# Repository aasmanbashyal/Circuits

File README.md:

# Circuits
This repo consists the all the circuits i have build

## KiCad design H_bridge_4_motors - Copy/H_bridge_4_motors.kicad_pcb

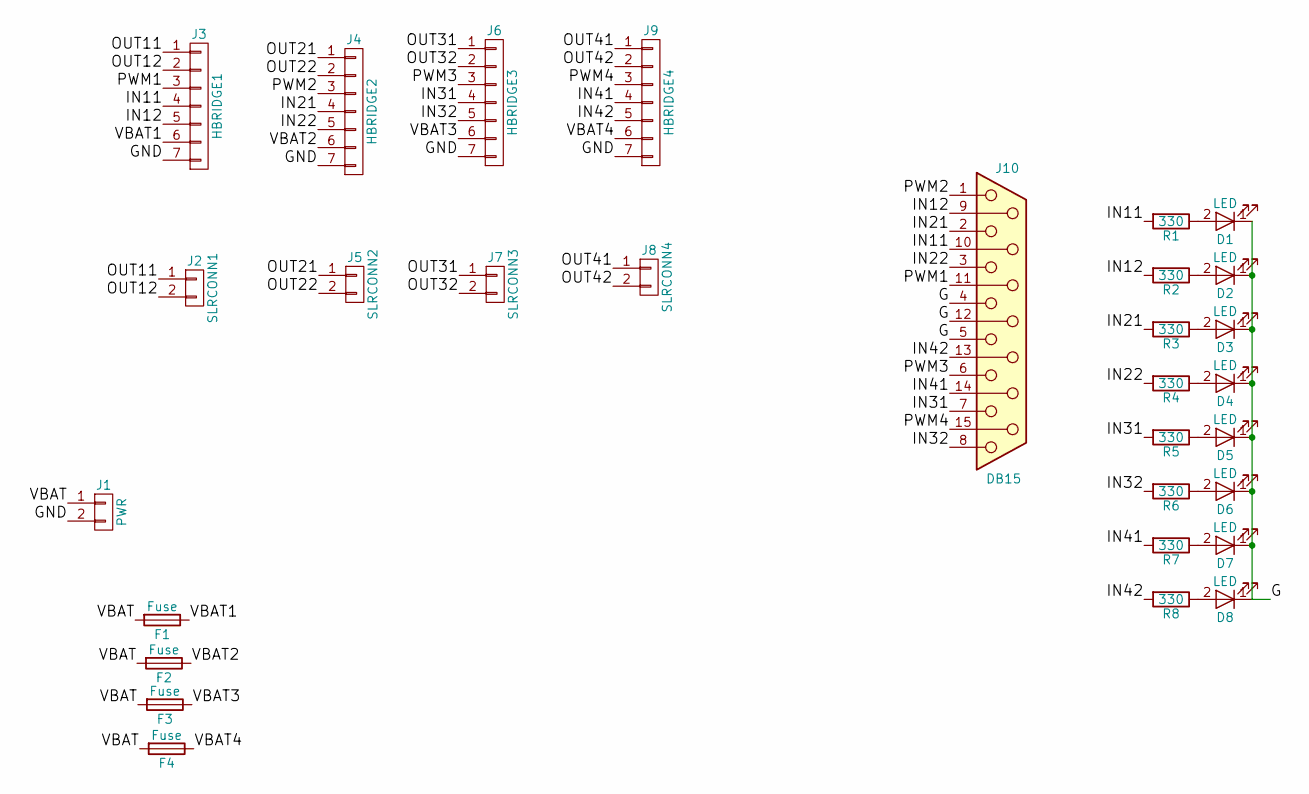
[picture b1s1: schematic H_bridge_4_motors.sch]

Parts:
D1, D2, D3, D4, D5, D6, D7, D8: LED; LED_D3.0mm
F1, F2, F3, F4: Fuse; Fuse_Holder
J1: PWR; Solar_Connector
J2: SLRCONN1; Solar_Connector
J3: HBRIDGE1; Bridge
J4: HBRIDGE2; Bridge
J5: SLRCONN2; Solar_Connector
J6: HBRIDGE3; Bridge
J7: SLRCONN3; Solar_Connector
J8: SLRCONN4; Solar_Connector
J9: HBRIDGE4; Bridge
J10: DB15
R1, R2, R3, R4, R5, R6, R7, R8: 330; Resistor_small

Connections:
/G: D1.1 (K), D2.1 (K), D3.1 (K), D4.1 (K), D5.1 (K), D6.1 (K), D7.1 (K), D8.1 (K), J10.4, J10.5, J10.12
/GND: J1.2, J3.7, J4.7, J6.7, J9.7
/IN11: J3.4, J10.10, R1.2
/IN12: J3.5, J10.9, R2.2
/IN21: J4.4, J10.2, R3.2
/IN22: J4.5, J10.3, R4.2
/IN31: J6.4, J10.7, R5.2
/IN32: J6.5, J10.8, R6.2
/IN41: J9.4, J10.14, R7.2
/IN42: J9.5, J10.13, R8.2
/OUT11: J2.1, J3.1
/OUT12: J2.2, J3.2
/OUT21: J4.1, J5.1
/OUT22: J4.2, J5.2
/OUT31: J6.1, J7.1
/OUT32: J6.2, J7.2
/OUT41: J8.1, J9.1
/OUT42: J8.2, J9.2
/PWM1: J3.3, J10.11 (P111)
/PWM2: J4.3, J10.1
/PWM3: J6.3, J10.6
/PWM4: J9.3, J10.15
/VBAT: F1.2, F2.2, F3.2, F4.2, J1.1
/VBAT1: F1.1, J3.6
/VBAT2: F2.1, J4.6
/VBAT3: F3.1, J6.6
/VBAT4: F4.1, J9.6
unnamed: D1.2 (A), R1.1
unnamed: D2.2 (A), R2.1
unnamed: D3.2 (A), R3.1
unnamed: D4.2 (A), R4.1
unnamed: D5.2 (A), R5.1
unnamed: D6.2 (A), R6.1
unnamed: D7.2 (A), R7.1
unnamed: D8.2 (A), R8.1

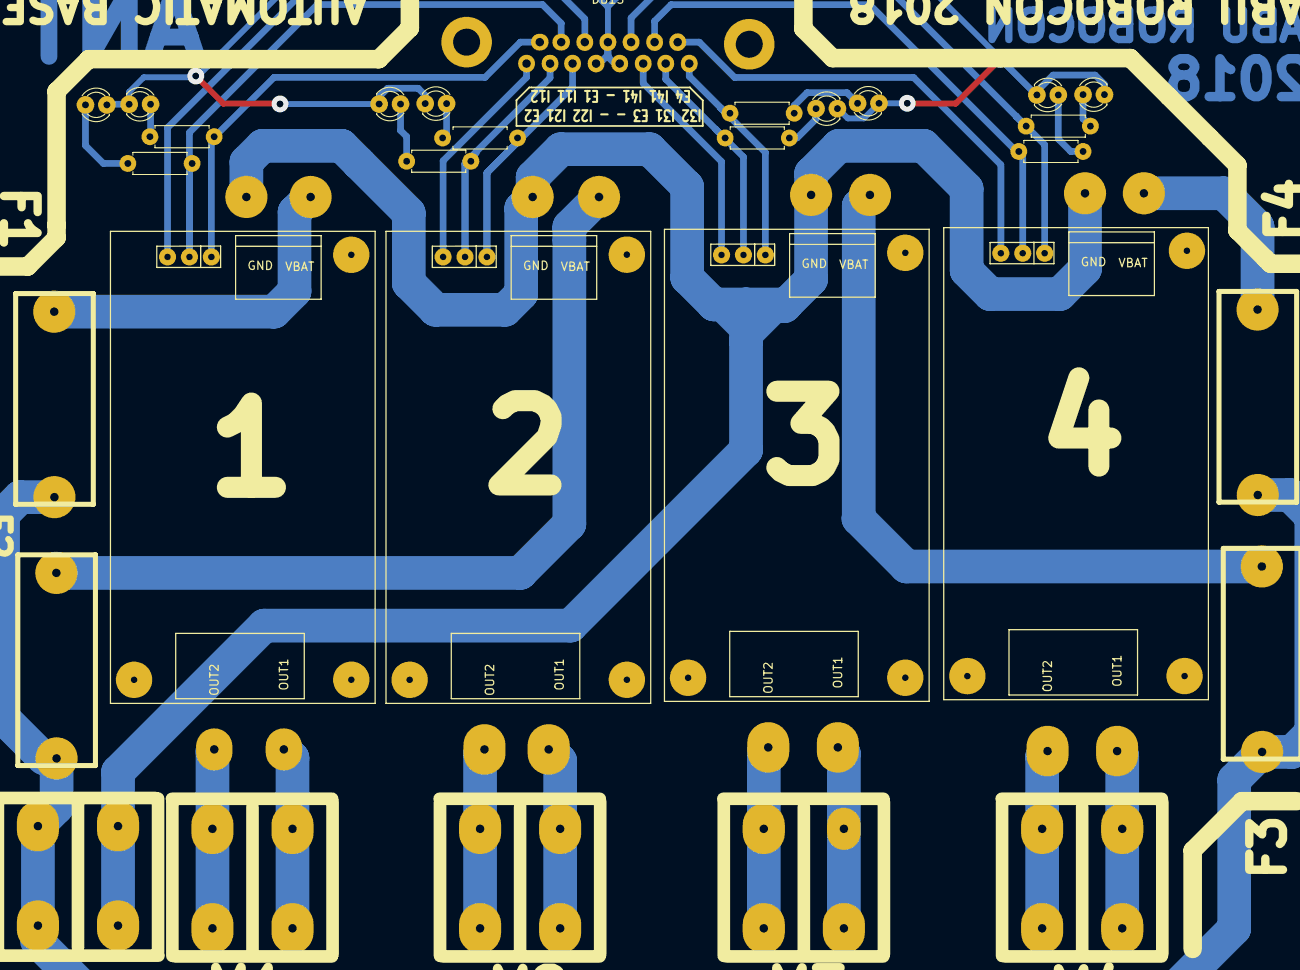
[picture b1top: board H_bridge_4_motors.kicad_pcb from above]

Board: 2 copper layers, 30 parts (0 on the bottom side), 35 nets.

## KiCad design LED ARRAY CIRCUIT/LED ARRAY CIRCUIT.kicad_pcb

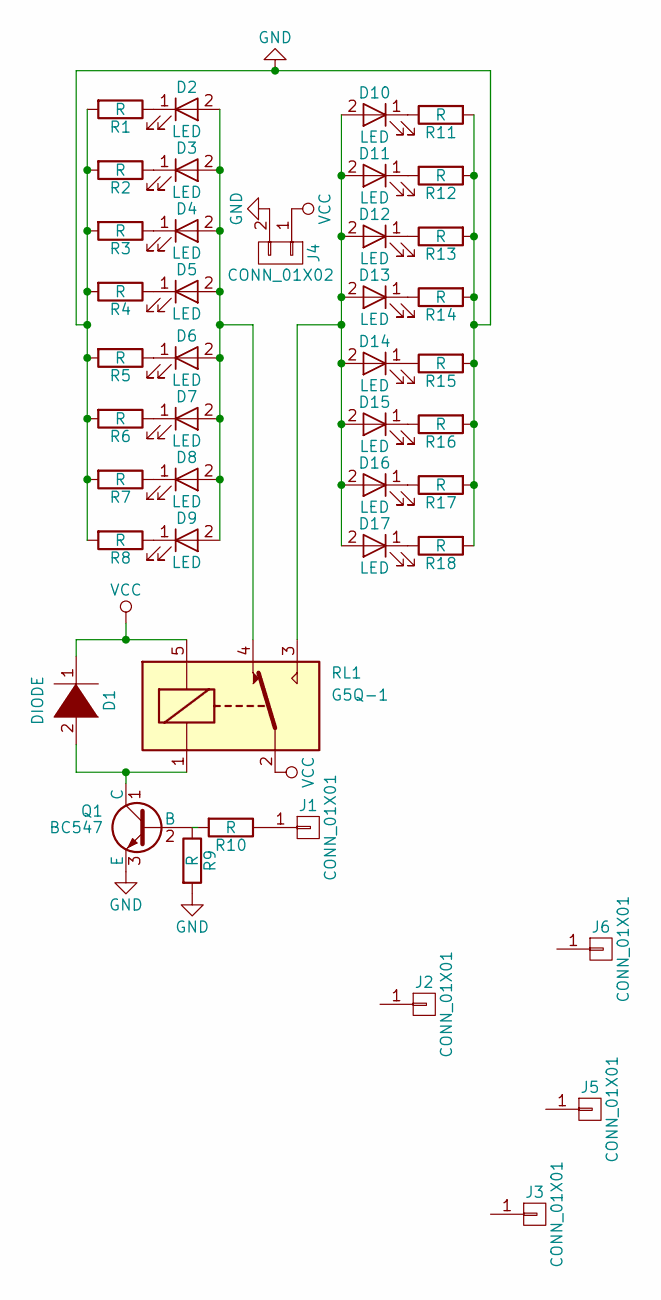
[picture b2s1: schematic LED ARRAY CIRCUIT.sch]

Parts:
D1: DIODE; Diode_Small
D2, D3, D4, D5, D6, D7, D8, D9, D10, D11, D12, D13, D14, D15, D16, D17: LED; LED_D3.0mm
J1: CONN_01X01; Pin_Header_Straight_1x01_Pitch2.00mm
J2, J3, J5, J6: CONN_01X01; 1pin
J4: CONN_01X02; Connector_Bornier_2
Q1: BC547
R1, R2, R3, R4, R5, R6, R7, R8, R9, R10, R11, R12, R13, R14, R15, R16, R17, R18: R; Resistor_small
RL1: G5Q-1; Relay_6V

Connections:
GND: J4.2, Q1.3 (E), R1.2, R2.2, R3.2, R4.2, R5.2, R6.2, R7.2, R8.2, R9.2, R11.2, R12.2, R13.2, R14.2, R15.2, R16.2, R17.2, R18.2
unnamed: D1.2 (A), Q1.1 (C), RL1.1
unnamed: D2.1 (K), R1.1
unnamed: D2.2 (A), D3.2 (A), D4.2 (A), D5.2 (A), D6.2 (A), D7.2 (A), D8.2 (A), D9.2 (A), RL1.4
unnamed: D3.1 (K), R2.1
unnamed: D4.1 (K), R3.1
unnamed: D5.1 (K), R4.1
unnamed: D6.1 (K), R5.1
unnamed: D7.1 (K), R6.1
unnamed: D8.1 (K), R7.1
unnamed: D9.1 (K), R8.1
unnamed: D10.1 (K), R11.1
unnamed: D10.2 (A), D11.2 (A), D12.2 (A), D13.2 (A), D14.2 (A), D15.2 (A), D16.2 (A), D17.2 (A), RL1.3
unnamed: D11.1 (K), R12.1
unnamed: D12.1 (K), R13.1
unnamed: D13.1 (K), R14.1
unnamed: D14.1 (K), R15.1
unnamed: D15.1 (K), R16.1
unnamed: D16.1 (K), R17.1
unnamed: D17.1 (K), R18.1
unnamed: J1.1, R10.1
unnamed: Q1.2 (B), R9.1, R10.2
VCC: D1.1 (K), J4.1, RL1.2, RL1.5

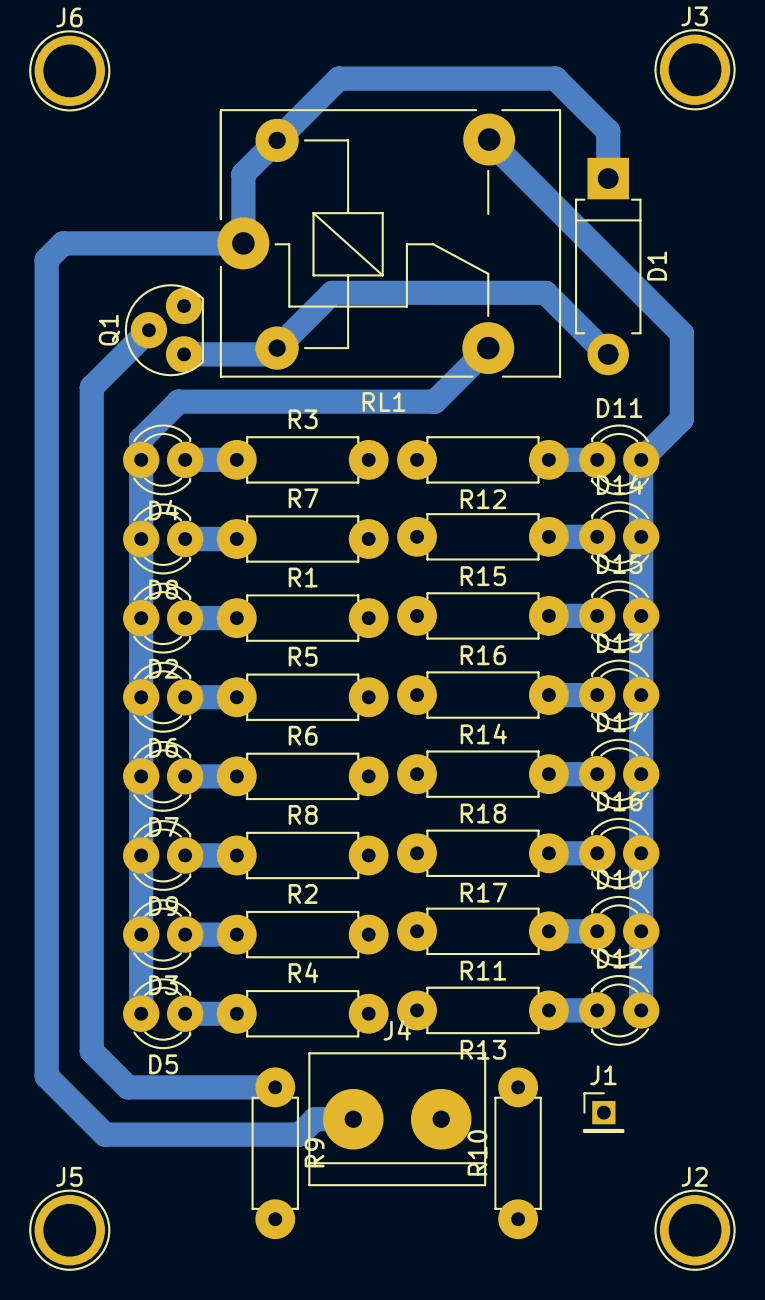
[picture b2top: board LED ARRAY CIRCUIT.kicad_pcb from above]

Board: 2 copper layers, 43 parts (0 on the bottom side), 23 nets.

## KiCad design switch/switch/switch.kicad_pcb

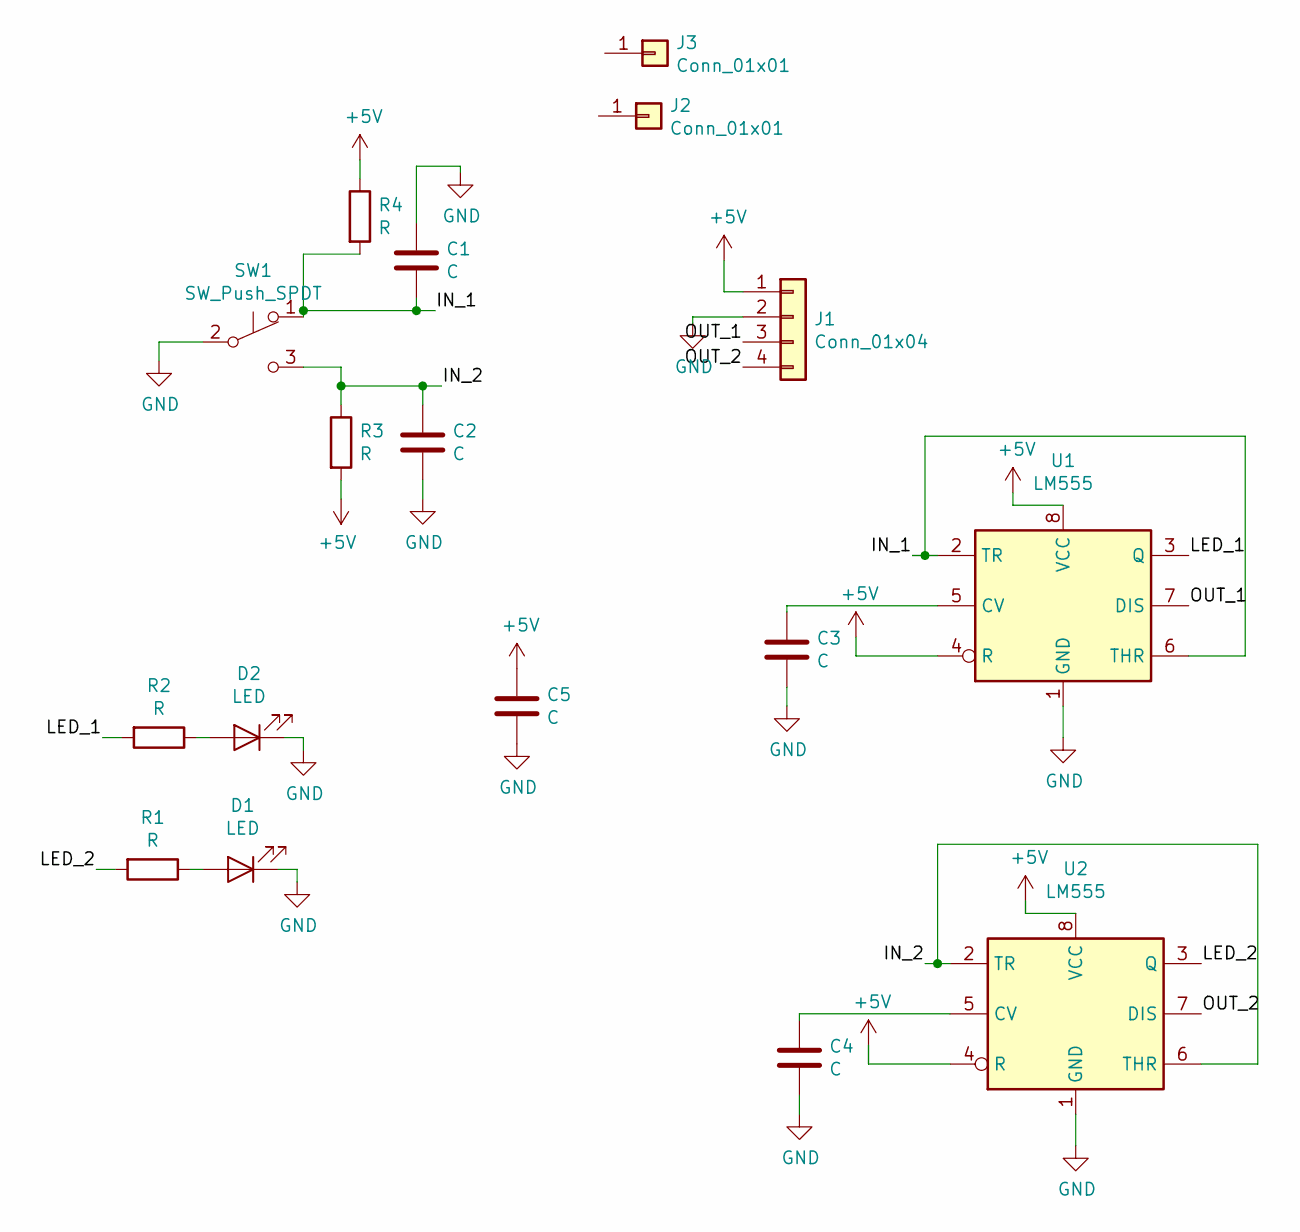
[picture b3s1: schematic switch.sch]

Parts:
C1, C2, C3, C4, C5: C; Capacitor_Disc_Small
D1, D2: LED; LED_D5.0mm
J1: Conn_01x04; JST_EH_B04B-EH-A_04x2.50mm_Straight
J2, J3: Conn_01x01; Banana_Jack_1Pin
R1, R2, R3, R4: R; Resistor_small
SW1: SW_Push_SPDT; toggle_small
U1, U2: LM555; DIP-8_W7.62mm

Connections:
+5V: C5.1, J1.1, R3.2, R4.1, U1.4 (R), U1.8 (VCC), U2.4 (R), U2.8 (VCC)
/IN_1: C1.2, R4.2, SW1.1 (A), U1.2 (TR), U1.6 (THR)
/IN_2: C2.1, R3.1, SW1.3 (C), U2.2 (TR), U2.6 (THR)
/LED_1: R2.2, U1.3 (Q)
/LED_2: R1.2, U2.3 (Q)
/OUT_1: J1.3, U1.7 (DIS)
/OUT_2: J1.4, U2.7 (DIS)
GND: C1.1, C2.2, C3.2, C4.2, C5.2, D1.1 (K), D2.1 (K), J1.2, SW1.2 (B), U1.1 (GND), U2.1 (GND)
unnamed: C3.1, U1.5 (CV)
unnamed: C4.1, U2.5 (CV)
unnamed: D1.2 (A), R1.1
unnamed: D2.2 (A), R2.1

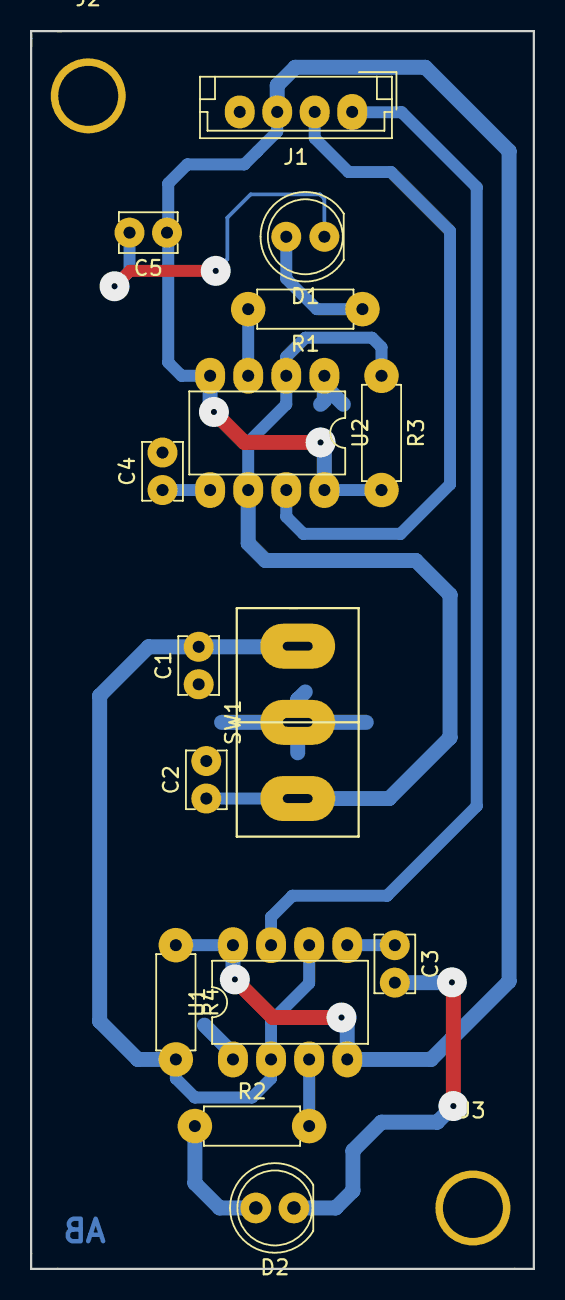
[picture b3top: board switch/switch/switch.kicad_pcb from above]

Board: 2 copper layers, 33.5 x 82.6 mm, 17 parts (0 on the bottom side), 12 nets.

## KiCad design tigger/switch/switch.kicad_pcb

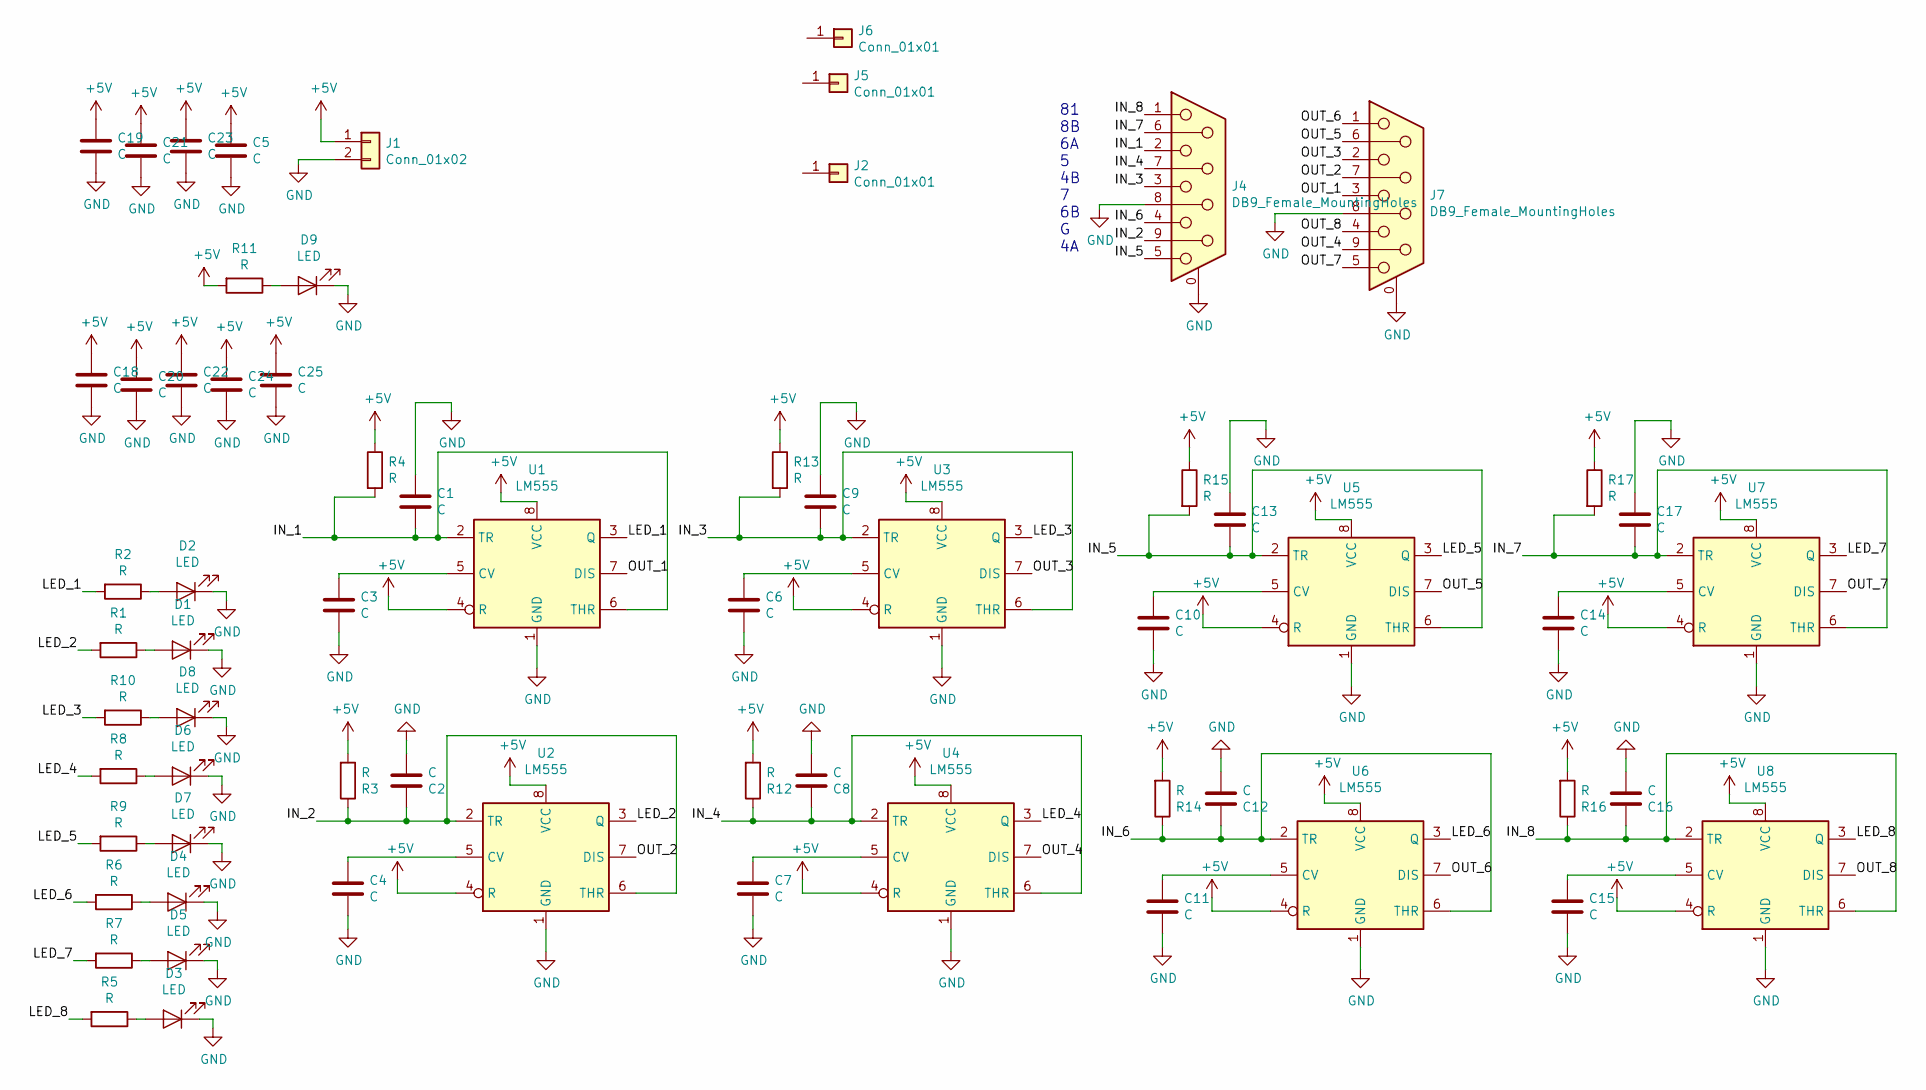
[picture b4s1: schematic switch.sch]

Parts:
C1, C2, C3, C4, C5, C6, C7, C8, C9, C10, C11, C12, C13, C14, C15, C16, C17, C18, C19, C20, C21, C22, C23, C24, C25: C; Capacitor_Disc_Small
D1, D2, D3, D4, D5, D6, D7, D8, D9: LED; LED_D3.0mm
J1: Conn_01x02; Connector_Bornier_2
J2, J5, J6: Conn_01x01; Banana_Jack_1Pin
J4, J7: DB9_Female_MountingHoles; Connector_DB_9
R1, R2, R3, R4, R5, R6, R7, R8, R9, R10, R11, R12, R13, R14, R15, R16, R17: R; Resistor_small
U1, U2, U3, U4, U5, U6, U7, U8: LM555; DIP-8_W7.62mm

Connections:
+5V: C5.1, C18.1, C19.1, C20.1, C21.1, C22.1, C23.1, C24.1, C25.1, J1.1, R3.2, R4.1, R11.2, R12.2, R13.1, R14.2, R15.1, R16.2, R17.1, U1.4 (R), U1.8 (VCC), U2.4 (R), U2.8 (VCC), U3.4 (R), U3.8 (VCC), U4.4 (R), U4.8 (VCC), U5.4 (R), U5.8 (VCC), U6.4 (R), U6.8 (VCC), U7.4 (R), U7.8 (VCC), U8.4 (R), U8.8 (VCC)
/IN_1: C1.2, J4.2, R4.2, U1.2 (TR), U1.6 (THR)
/IN_2: C2.1, J4.9, R3.1, U2.2 (TR), U2.6 (THR)
/IN_3: C9.2, J4.3, R13.2, U3.2 (TR), U3.6 (THR)
/IN_4: C8.1, J4.7, R12.1, U4.2 (TR), U4.6 (THR)
/IN_5: C13.2, J4.5, R15.2, U5.2 (TR), U5.6 (THR)
/IN_6: C12.1, J4.4, R14.1, U6.2 (TR), U6.6 (THR)
/IN_7: C17.2, J4.6, R17.2, U7.2 (TR), U7.6 (THR)
/IN_8: C16.1, J4.1, R16.1, U8.2 (TR), U8.6 (THR)
/LED_1: R2.2, U1.3 (Q)
/LED_2: R1.2, U2.3 (Q)
/LED_3: R10.2, U3.3 (Q)
/LED_4: R8.2, U4.3 (Q)
/LED_5: R9.2, U5.3 (Q)
/LED_6: R6.2, U6.3 (Q)
/LED_7: R7.2, U7.3 (Q)
/LED_8: R5.2, U8.3 (Q)
/OUT_1: J7.3, U1.7 (DIS)
/OUT_2: J7.7, U2.7 (DIS)
/OUT_3: J7.2, U3.7 (DIS)
/OUT_4: J7.9, U4.7 (DIS)
/OUT_5: J7.6, U5.7 (DIS)
/OUT_6: J7.1, U6.7 (DIS)
/OUT_7: J7.5, U7.7 (DIS)
/OUT_8: J7.4, U8.7 (DIS)
GND: C1.1, C2.2, C3.2, C4.2, C5.2, C6.2, C7.2, C8.2, C9.1, C10.2, C11.2, C12.2, C13.1, C14.2, C15.2, C16.2, C17.1, C18.2, C19.2, C20.2, C21.2, C22.2, C23.2, C24.2, C25.2, D1.1 (K), D2.1 (K), D3.1 (K), D4.1 (K), D5.1 (K), D6.1 (K), D7.1 (K), D8.1 (K), D9.1 (K), J1.2, J4.0 (PAD), J4.8, J7.0 (PAD), J7.8, U1.1 (GND), U2.1 (GND), U3.1 (GND), U4.1 (GND), U5.1 (GND), U6.1 (GND), U7.1 (GND), U8.1 (GND)
unnamed: C3.1, U1.5 (CV)
unnamed: C4.1, U2.5 (CV)
unnamed: C6.1, U3.5 (CV)
unnamed: C7.1, U4.5 (CV)
unnamed: C10.1, U5.5 (CV)
unnamed: C11.1, U6.5 (CV)
unnamed: C14.1, U7.5 (CV)
unnamed: C15.1, U8.5 (CV)
unnamed: D1.2 (A), R1.1
unnamed: D2.2 (A), R2.1
unnamed: D3.2 (A), R5.1
unnamed: D4.2 (A), R6.1
unnamed: D5.2 (A), R7.1
unnamed: D6.2 (A), R8.1
unnamed: D7.2 (A), R9.1
unnamed: D8.2 (A), R10.1
unnamed: D9.2 (A), R11.1

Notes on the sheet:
81 8B 6A 5 4B 7 6B G 4A

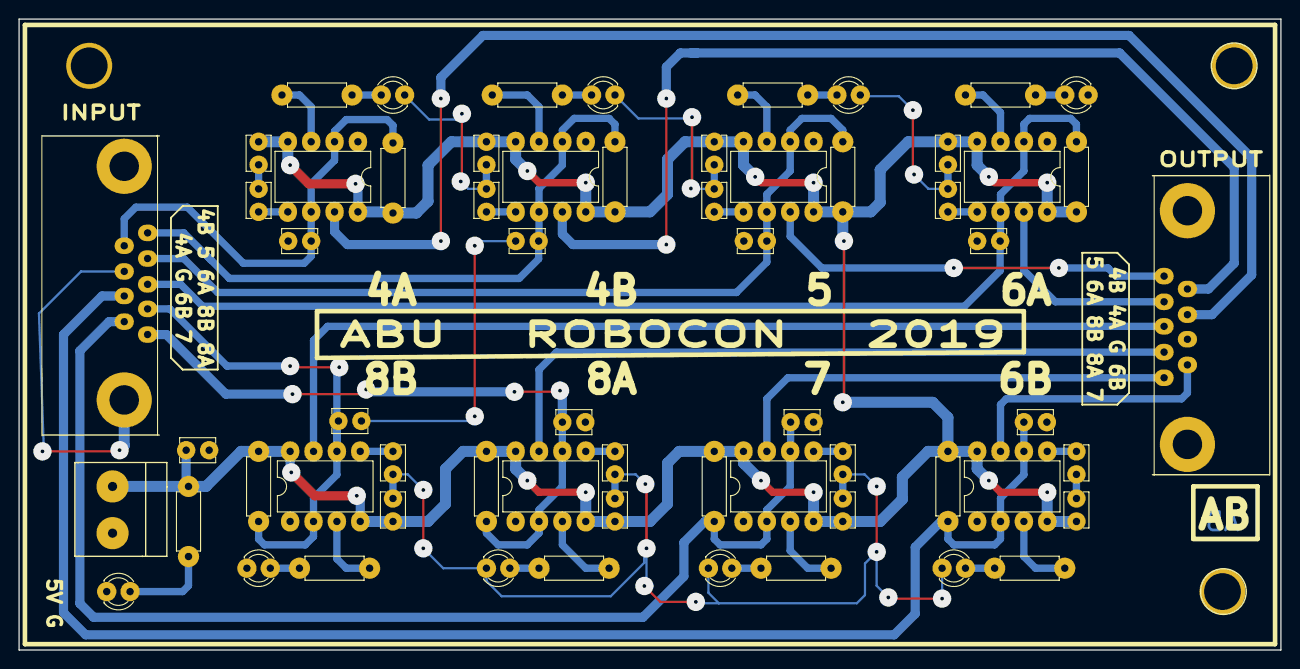
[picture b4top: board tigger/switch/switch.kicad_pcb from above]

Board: 2 copper layers, 137.2 x 68.6 mm, 65 parts (0 on the bottom side), 43 nets.

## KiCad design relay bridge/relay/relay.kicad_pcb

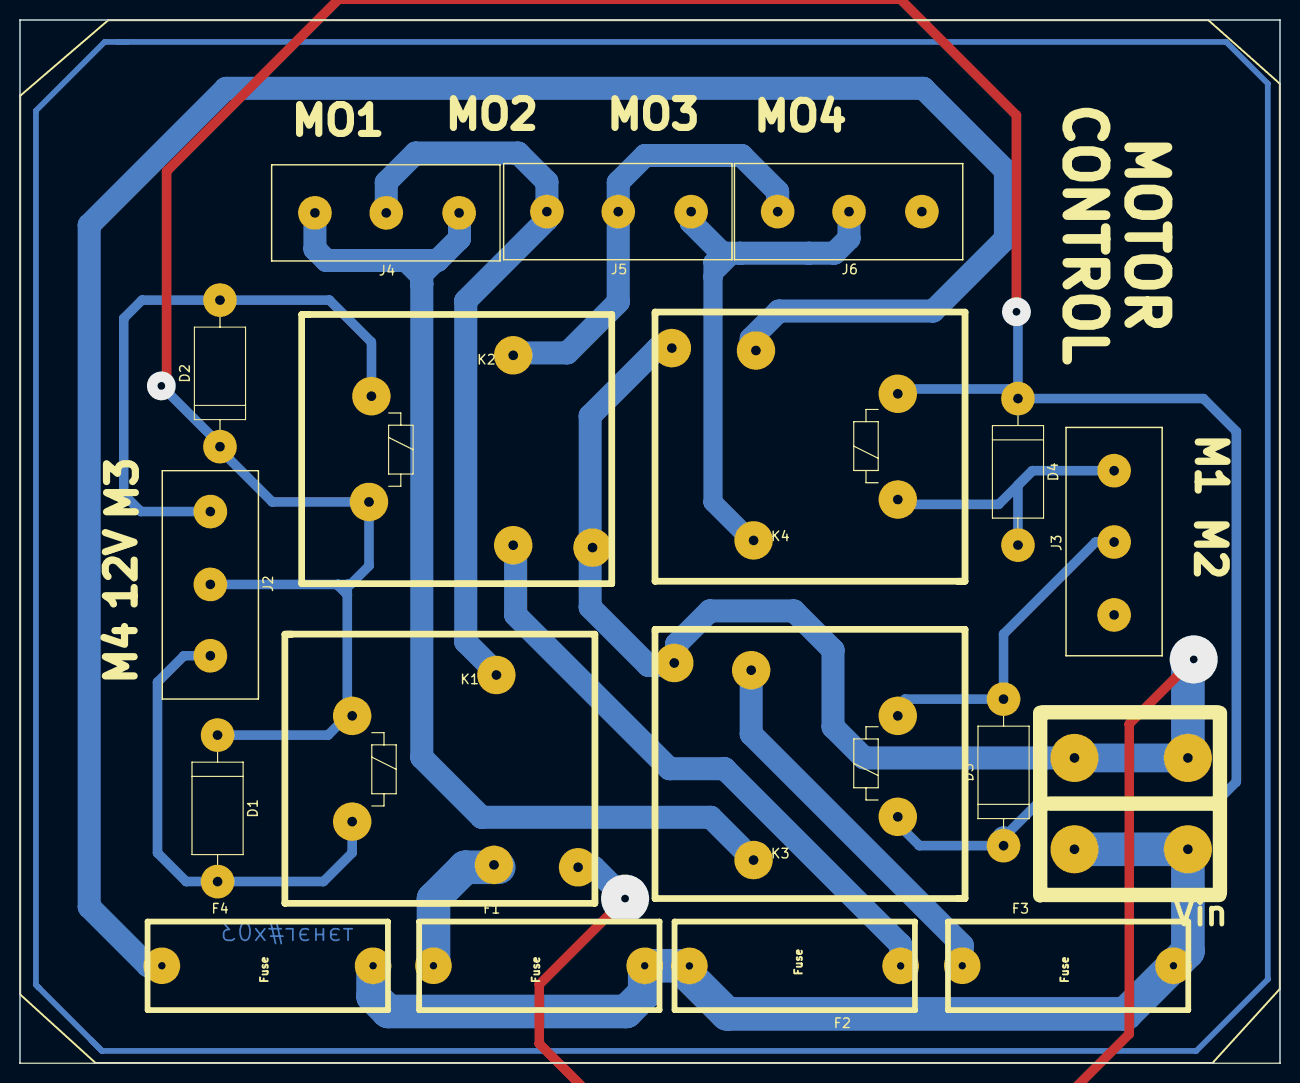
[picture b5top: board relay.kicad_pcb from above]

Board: 2 copper layers, 131.1 x 108.5 mm, 18 parts (0 on the bottom side), 15 nets.

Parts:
D1, D2, D3, D4: DIODE; Diode_Medium
F1, F2, F3, F4: Fuse; Fuse_Holder
J1: Conn_01x02; Solar_Connector
J2, J3, J4, J5, J6: Conn_01x03; Large_Connector_Bornier_3
K1, K2, K3, K4: DIPxx-1Cxx-51x; Relay_HLS_MEDIUM

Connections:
+12V: F1.1, F2.1, F3.1, F4.1, J1.2
/1: D1.2, D2.2, D3.2, D4.2, J2.2, K1.2, K2.6, K3.2, K4.6
/m1: D4.1, J3.3, K4.2
/m2: D3.1, J3.2, K3.6
/m3: D2.1, J2.1, K2.2
/m4: D1.1, J2.3, K1.6
/o1: J4.2, J5.3, K1.7
/o2: J4.1, J4.3, K3.7
/o3: J5.1, J6.2, K4.7
/o4: J5.2, J6.3, K2.7
GND: J1.1, K1.14, K2.14, K3.14, K4.14
unnamed: F1.2, K1.1
unnamed: F2.2, K2.1
unnamed: F3.2, K3.1
unnamed: F4.2, K4.1

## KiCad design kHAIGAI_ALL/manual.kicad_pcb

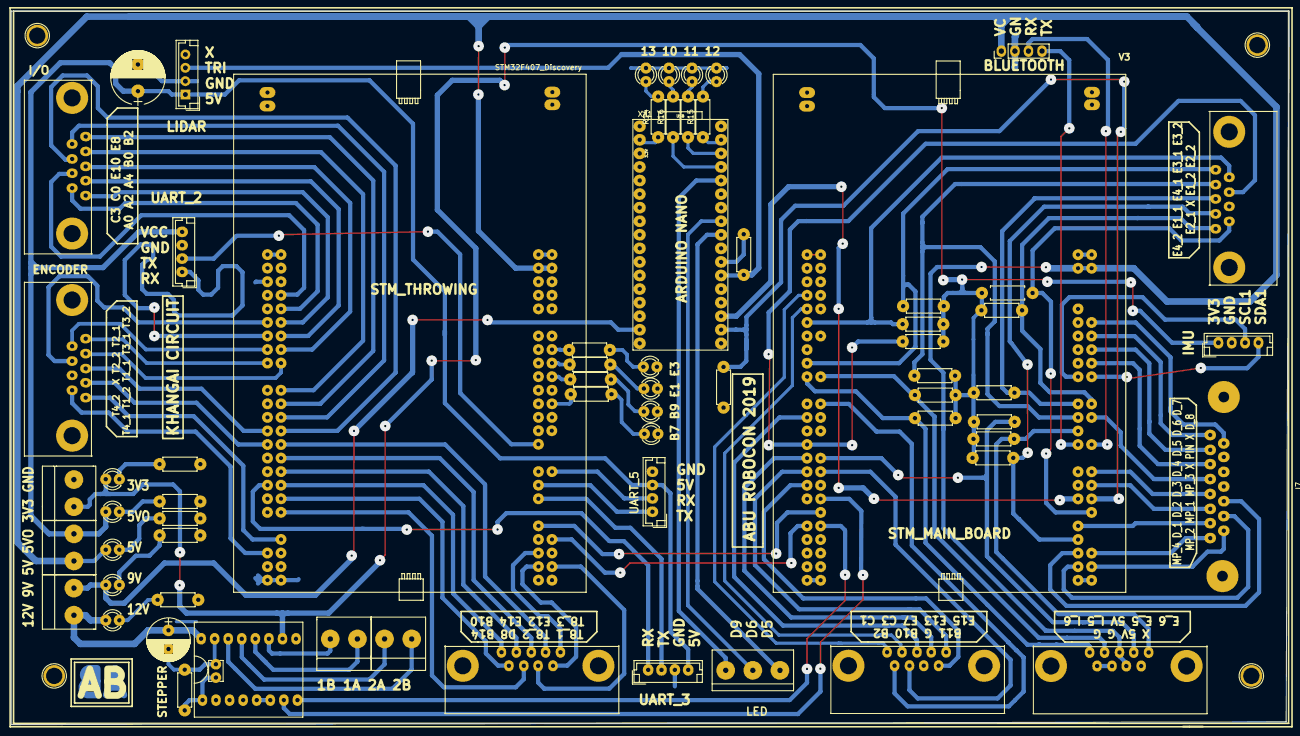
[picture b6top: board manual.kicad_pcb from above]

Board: 2 copper layers, 239.3 x 133.6 mm, 71 parts (0 on the bottom side), 112 nets.

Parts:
C1: C; Capacitor_Disc_Small
C2: CP; Capacitor_100uF
C3: CP; Capacitor_1000uF
D1: D_Zener; Resistor_small
D2, D3, D4, D5, D6, D7, D8, D9, D10, D11, D12, D13, D14: LED; LED_D3.0mm
J1, J2, J3, J9, J11: Conn_01x02; Connector_Bornier_2
J4, J12, J15, J23, J24: Conn_01x04; JST_EH_B04B-EH-A_04x2.50mm_Straight
J5, J13, J14, J16, J17, J18: DB9_Female_MountingHoles; Connector_DB_9
J6: Conn_01x04; Pin_Header_Straight_1x04_Pitch2.54mm
J7: DB15_Female_MountingHoles; Connector_DB15
J8: Conn_01x03; Connector_Bornier_3
J10: Conn_02x08_Counter_Clockwise; A4998
J19, J20, J21, J22: Conn_01x01_Female; 1pin
R7, R8, R9, R10, R11, R12, R13, R14, R15, R16, R17, R18, R19, R20, R21, R22, R23, R24, R25, R26, R27, R28, R29, R31, R33, R36, R40: R; Resistor_small
U1, U2: STM32F407_Discovery
XA1: Arduino_Nano_Socket

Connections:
+3V3: D6.2, J3.2, J4.1, J10.10, R18.1, R19.1, R20.1, R21.1, R22.1, R23.1, R24.1, R25.1, R26.1, R27.1, R28.1, R29.1
+5V: D4.2, J2.2, J6.1, J14.3, J14.7, U1.53, U1.54, U2.53, U2.54
+5VA: C3.1, D5.2, J2.1, J12.1, J15.4, J23.4, J24.4
+9V: D2.2, J1.1, XA1.VIN
+12V: C2.1, D3.2, J1.2, J10.16
/1A: J10.12, J11.2
/1B: J10.11, J11.1
/2A: J9.1, J10.13
/2B: J9.2, J10.14
/12C1_SCL: J4.3, U1.69
/12C1_SDA: J4.4, U1.70
/D_1: J7.7, U1.91
/D_2: J7.6, U1.86
/D_3: J7.5, U1.84
/D_4: J7.4, U1.76
/D_5: J7.3, U1.68
/D_6: J7.2, U1.66
/D_7: J7.1, U1.64
/D_8: J7.9, U1.62
/EM_3_CH1: J13.2, R22.2, U1.75
/EM_3_CH2: J13.1, R23.2, U1.17
/EN_1_CH1: J13.4, R18.2, U1.93
/EN_1_CH2: J13.7, R19.2, U1.29
/EN_2_CH1: J13.9, R20.2, U1.90
/EN_2_CH2: J13.6, R21.2, U1.11
/EN_4_CH1: J13.3, R24.2, U1.73
/EN_4_CH2: J13.5, R25.2, U1.74
/EN_5: J14.2, R26.2, U1.32
/EN_6: J14.1, R28.2, U1.77
/G_01: J5.9, U1.24
/G_02: J5.8, U1.34
/G_03: J5.5, U1.7
/G_04: J5.4, U1.9
/G_08: J5.3, U1.25
/G_09: J5.2, U1.31
/G_10: J5.1, U1.33
/G_11: J5.6, U1.35
/IN_5: J14.4, R27.2, U1.20
/IN_6: J14.5, R29.2, U1.19
/M_PWM_1: J7.14, U1.97
/M_PWM_2: J7.15, U1.98
/M_PWM_3: J7.13, U1.95
/M_PWM_4: J7.8, U1.96
/S1_I/O: J10.8, U1.42
/S1_PWM: J10.7, U1.38
/UART2_RX: J6.3, U1.80
/UART2_TX: J6.4, U1.79
/USART3_RX: U1.41, U2.94
/USART3_TX: U1.40, U2.91
/USART4_RX: D1.1, U1.88, XA1.D1
/USART4_TX: U1.87, XA1.D0
/throw/I_1: R17.1, U2.66
/throw/I_2: R31.1, U2.68
/throw/I_3: R33.1, U2.70
/throw/I_4: R36.1, U2.74
/throw/PA0: J17.1, U2.12
/throw/PA2: J17.2, U2.14
/throw/PA4: J17.3, U2.16
/throw/PB0: J17.4, U2.22
/throw/PB2: J17.5, U2.24
/throw/PB10: J18.4, U2.34
/throw/PB12: J18.5, U2.36
/throw/PB14: J18.9, U2.38
/throw/PC0: J17.7, U2.8
/throw/PC3: J17.6, U2.10
/throw/PD8: J18.8, U2.40
/throw/PE8: J17.9, U2.26
/throw/PE10: J17.8, U2.28
/throw/PE12: J18.2, U2.30
/throw/PE14: J18.3, U2.32
/throw/T4_CH1: J16.1, U2.44
/throw/T4_CH2: J16.6, U2.45
/throw/T8_CH1: J18.6, U2.97
/throw/T8_CH2: J18.7, U2.98
/throw/T8_CH3: J18.1, U2.95
/throw/TIM1_CH1: J16.3, U2.27
/throw/TIM1_CH2: J16.2, U2.29
/throw/TIM2_CH1: J16.9, U2.15
/throw/TIM2_CH2: J16.8, U2.11
/throw/TIM3_CH1: J16.4, U2.18
/throw/TIM3_CH2: J16.5, U2.17
/throw/U2_RX: J23.2, U2.13
/throw/U2_TX: J23.1, U2.79
/throw/U3_RX: J24.1, U2.35
/throw/U3_TX: J24.2, U2.87
/throw/U5_RX: J15.2, U2.84
/throw/U5_TX: J15.1, U2.85
GND: C1.1, C2.2, C3.2, D1.2, D7.1, D8.1, D9.1, D10.1, D11.1, D12.1, D13.1, D14.1, J3.1, J4.2, J5.0, J5.7, J6.2, J10.9, J10.15, J12.2, J14.8, J14.9, J15.3, J23.3, J24.3, R7.1, R9.1, R10.1, R11.1, R12.1, R13.1, U1.1, U1.2, U1.5, U1.23, U1.49, U1.50, U1.51, U1.52, U1.99, U1.100, U2.1, U2.2, U2.5, U2.49, U2.50, U2.51, U2.52, U2.99, U2.100, XA1.GND1, XA1.GND2
unnamed: C1.2, J10.1, R7.2
unnamed: D2.1, R9.2
unnamed: D3.1, R10.2
unnamed: D4.1, R11.2
unnamed: D5.1, R12.2
unnamed: D6.1, R13.2
unnamed: D7.2, R14.2
unnamed: D8.2, R15.2
unnamed: D9.2, R16.2
unnamed: D10.2, R17.2
unnamed: D11.2, R31.2
unnamed: D12.2, R33.2
unnamed: D13.2, R40.2
unnamed: D14.2, R36.2
unnamed: J8.1, XA1.D5
unnamed: J8.2, XA1.D6
unnamed: J8.3, XA1.D9
unnamed: J10.5, J10.6
unnamed: J12.3, R8.1, XA1.D2
unnamed: R8.2, XA1.D3
unnamed: R14.1, XA1.D13
unnamed: R15.1, XA1.D12
unnamed: R16.1, XA1.D10
unnamed: R40.1, XA1.D11

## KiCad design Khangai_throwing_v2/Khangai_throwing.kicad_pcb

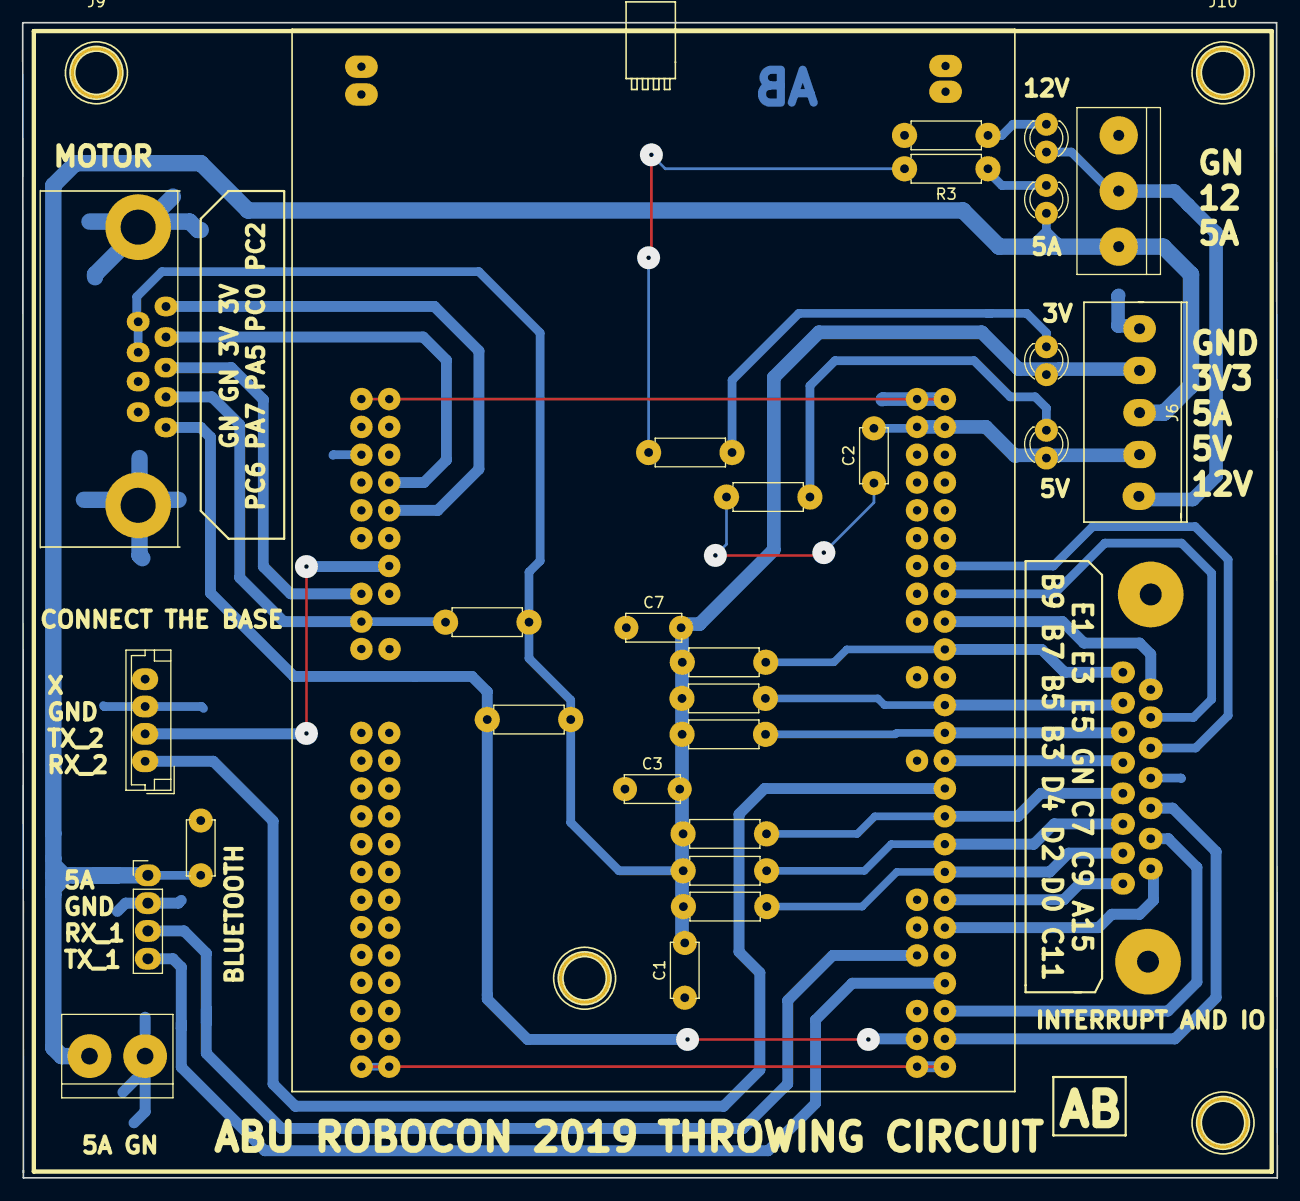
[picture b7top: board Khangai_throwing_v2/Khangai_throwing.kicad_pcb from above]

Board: 2 copper layers, 114.6 x 105.5 mm, 33 parts (0 on the bottom side), 32 nets.

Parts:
C1, C2, C3, C7, C8: C; Capacitor_Disc_Medium
D1, D2, D3, D4: LED; LED_D3.0mm
J1: Conn_01x04; Pin_Header_Straight_1x04_Pitch2.54mm
J2: Conn_01x02; bornier2
J3: DB9_Female; Connector_DB_9
J4: DB15_Female; Connector_DB15
J5: Conn_01x04; jst_4
J6: Conn_01x05; JST_5_BIG
J7: Conn_01x03; Connector_Bornier_3
J9, J10, J11, J12: Conn_01x01; BANANA_CONN_01
R1, R2, R3, R12, R14, R16, R17, R18, R19, R21, R22, R23: R; Resistor_small
U1: STM32F407_Discovery

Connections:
+3V3: C1.2, C3.2, C7.2, D2.2, J3.8, J3.9, J6.3, R14.1, R16.1, R17.1, R18.1, R19.1, R21.1, R22.1, R23.1
+5V: C2.2, D1.2, J6.4, U1.53, U1.54
+5VA: C8.1, D4.2, J1.1, J2.1, J6.2, J7.2
+12V: D3.2, J6.5, J7.1
/GPIO_1: J4.11, U1.64
/GPIO_2: J4.10, U1.66
/GPIO_3: J4.9, U1.68
/GPIO_4: J4.8, U1.88
/GPIO_5: J4.15, U1.90
/GPIO_6: J4.14, U1.96
/GPIO_7: J4.13, U1.98
/IN_1: J4.7, R17.2, U1.86
/IN_2: J4.6, R18.2, U1.84
/IN_3: J4.5, R19.2, U1.82
/IN_4: J4.4, U1.78
/IN_5: J4.3, R21.2, U1.76
/IN_6: J4.2, R22.2, U1.74
/IN_7: J4.1, R23.2, U1.70
/M2_CH1: J3.5, U1.10
/M2_CH2: J3.4, U1.8
/TIM2_CH1: J3.3, U1.15
/TIM3_CH1: J3.1, R14.2, U1.97
/TIM3_CH2: J3.2, R16.2, U1.17
/U1_RX: J1.3, U1.91
/U1_TX: J1.4, U1.94
/U2_RX: J5.1, U1.80
/U2_TX: J5.2, U1.14
GND: C1.1, C2.1, C3.1, C7.1, C8.2, J1.2, J2.2, J3.6, J3.7, J4.12, J5.3, J6.1, J7.3, R1.2, R2.2, R3.2, R12.2, U1.1, U1.2, U1.5, U1.49, U1.50, U1.51, U1.52, U1.99, U1.100
unnamed: D1.1, R1.1
unnamed: D2.1, R12.1
unnamed: D3.1, R2.1
unnamed: D4.1, R3.1
